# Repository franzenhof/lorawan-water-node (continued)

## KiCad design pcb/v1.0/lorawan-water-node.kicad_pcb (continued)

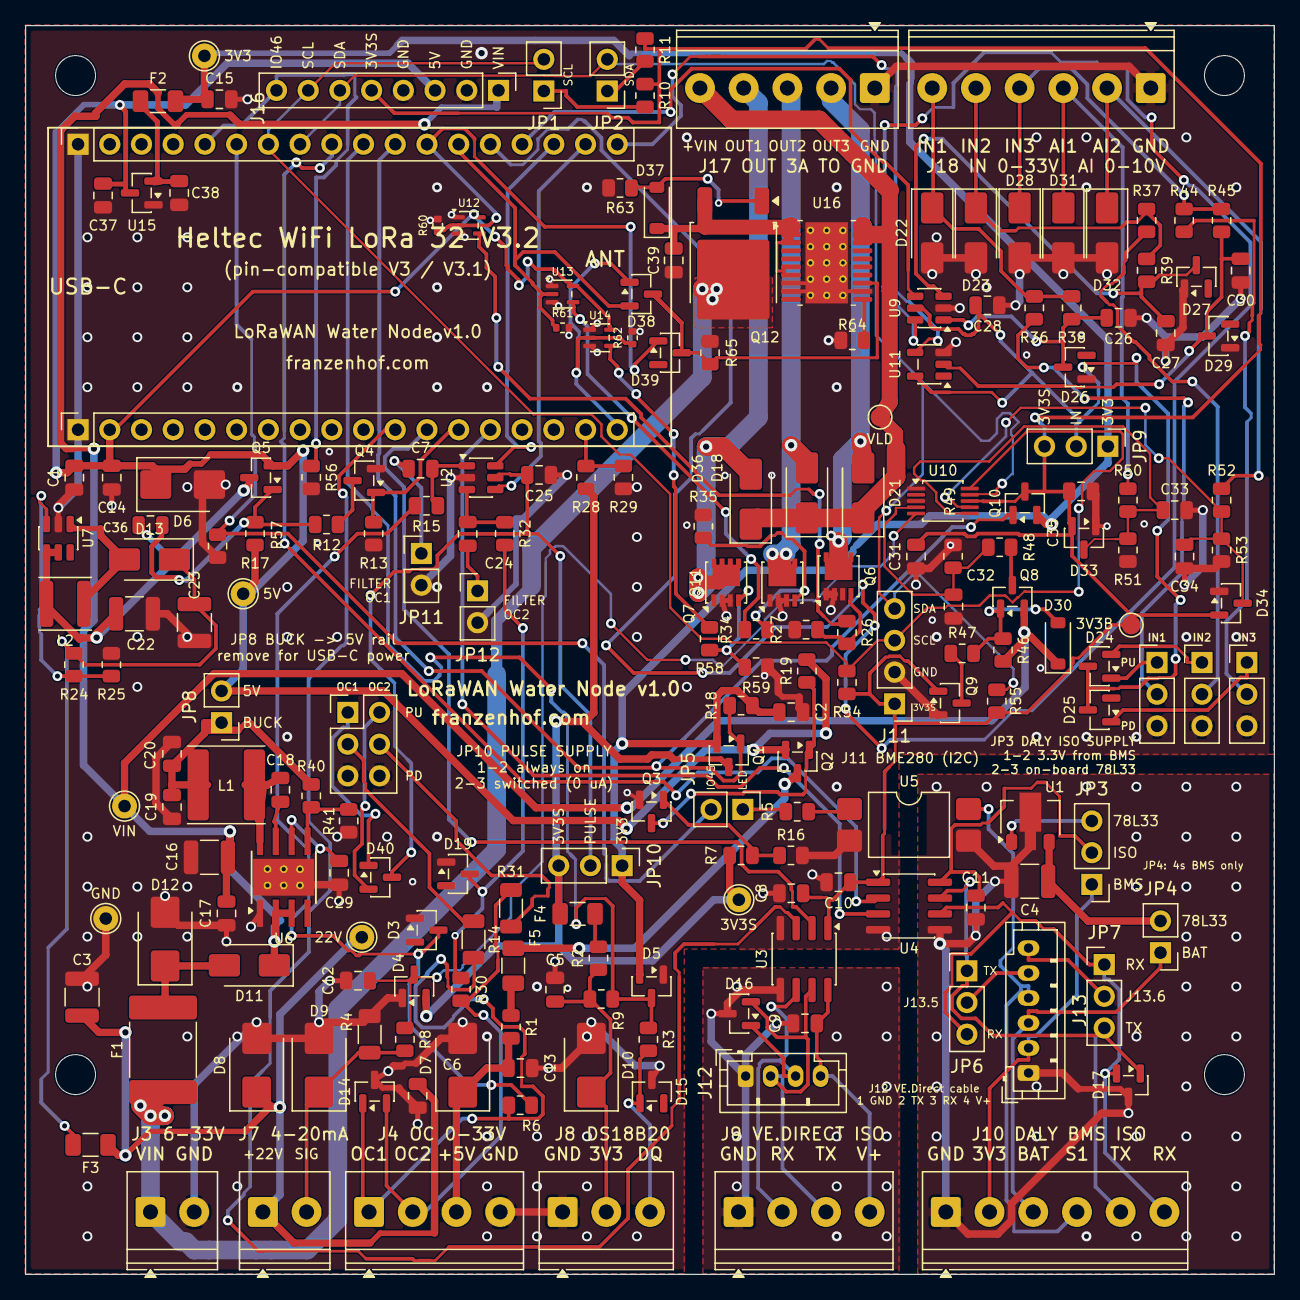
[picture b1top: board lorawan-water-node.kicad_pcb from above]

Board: 2 copper layers, 100.0 x 100.0 mm, 208 parts (0 on the bottom side), 118 nets.

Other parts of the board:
H1, H2, H3, H4: M3; MountingHole_3.2mm_M3

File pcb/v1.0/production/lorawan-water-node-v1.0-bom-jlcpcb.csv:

"Comment","Designator","Footprint","LCSC Part #","MPN"
"22uF 25V","C1,C2,C19,C20","Capacitor_SMD:C_0805_2012Metric","C45783","Samsung CL21A226MAQNNNE (25V X5R)"
"10uF 50V","C3,C4,C22,C23","Capacitor_SMD:C_1210_3225Metric","C596319","Yageo CC1210KKX7R9BB106"
"100nF","C5,C6,C8,C9,C10,C11,C12,C13,C14,C15,C18,C25,C26,C27,C28,C30,C31,C32,C33,C34,C35","Capacitor_SMD:C_0805_2012Metric","C49678","Yageo CC0805KRX7R9BB104"
"47nF","C7,C24","Capacitor_SMD:C_0805_2012Metric","C53134","Samsung CL21B473KBCNNNC (50V X7R, basic)"
"10uF 100V","C16","Capacitor_SMD:C_1210_3225Metric","C5156756","FS32X106K101EGG (100V X7R 1210)"
"220nF 100V","C17","Capacitor_SMD:C_0805_2012Metric","C513710","Yageo CC0805KKX7R0BB224 (100V X7R)"
"1uF","C29,C36,C37,C38","Capacitor_SMD:C_0805_2012Metric","C28323","Samsung CL21B105KBFNNNE (50V X7R)"
"100nF 100V","C39","Capacitor_SMD:C_0805_2012Metric","C28233","Samsung CL21B104KCFNNNE (100V X7R)"
"BZX84C5V6","D3,D19,D26,D27,D29","Package_TO_SOT_SMD:SOT-23","C82471","onsemi BZX84C5V6LT1G"
"BAT54S","D4,D5,D33,D34","Package_TO_SOT_SMD:SOT-23","C7420333","R+O BAT54S (preferred)"
"SMBJ6.0A","D6,D7","Diode_SMD:D_SMB","C113976","SMBJ6.0A"
"SMBJ24A","D8","Diode_SMD:D_SMB","C123819","SMBJ24A"
"SMBJ5.0A","D9","Diode_SMD:D_SMB","C78423","SMBJ5.0A"
"SMLVT3V3","D10","Diode_SMD:D_SMB","C283619","SMLVT3V3"
"SS210","D11,D13,D18,D21,D36","Diode_SMD:D_SMA","C14996","SS210 (100 V 2 A Schottky, basic)"
"SMBJ33CA","D12","Diode_SMD:D_SMB","C78420","SMBJ33CA (bidirectional)"
"PESD36VS2UT","D14","Package_TO_SOT_SMD:SOT-23","C85381","Nexperia PESD36VS2UT,215 (36 V, 2 lines)"
"PESD5V0S2BT","D15,D16,D17","Package_TO_SOT_SMD:SOT-23","C49338","Nexperia PESD5V0S2BT,215"
"SMAJ33CA","D22,D23,D28,D31,D32","Diode_SMD:D_SMA","C115251","SMAJ33CA (400 W, bidirectional)"
"BAS70-06","D24,D25,D40","Package_TO_SOT_SMD:SOT-23","C8651","Nexperia BAS70-06,215 (70 V Schottky, common anode)"
"BZT52C12","D30,D37","Diode_SMD:D_SOD-123","C19077410","BZT52C12 (preferred)"
"BAV70","D38,D39","Package_TO_SOT_SMD:SOT-23","C68978","BAV70 (common cathode, basic)"
"PTC 1.1A 60V","F1","Fuse:Fuse_2920_7451Metric","C3020148","BHFUSE BSMD2920-100-60V"
"PTC 0.25A","F2","Fuse:Fuse_1206_3216Metric","C70068","nSMD025 (16V)"
"PTC 0.05A","F3,F4","Fuse:Fuse_1206_3216Metric","C7542924","Littelfuse 1206L005/60NR (60V)"
"PTC 0.1A","F5","Fuse:Fuse_1206_3216Metric","C70065","nSMD010 (60V)"
"22uH","L1","Inductor_SMD:L_Sunlord_SWPA6045S","C83454","Sunlord SWPA6045S220MT"
"22uH","L2","Inductor_SMD:L_Sunlord_SWPA4030S","C83472","Sunlord SWPA4030S220MT"
"AO3401A","Q1,Q2,Q5,Q10","Package_TO_SOT_SMD:SOT-23","C15127","AO3401A"
"AO3400A","Q3,Q4","Package_TO_SOT_SMD:SOT-23","C20917","AOS AO3400A"
"AON7264E","Q6,Q7,Q11","Package_SO:Vishay_PowerPAK_1212-8_Single","C431191","AOS AON7264E (60 V N-MOSFET, DFN 3.3x3.3)"
"SI2309CDS","Q8","Package_TO_SOT_SMD:SOT-23","C10493","Vishay SI2309CDS-T1-GE3"
"2N7002","Q9","Package_TO_SOT_SMD:SOT-23","C8545","2N7002 (60 V)"
"NCE60P50K","Q12","Package_TO_SOT_SMD:TO-252-2","C130104","NCE60P50K (60 V P-MOSFET, TO-252)"
"10","R1,R2","Resistor_SMD:R_0805_2012Metric","C17415","UniOhm 0805W8F100JT5E"
"33","R3","Resistor_SMD:R_0805_2012Metric","C17634","UniOhm 0805W8F330JT5E"
"120 0.1%","R4","Resistor_SMD:R_1206_3216Metric","C870389","Yageo RT1206BRD07120RL"
"220","R5,R26,R34,R58","Resistor_SMD:R_0805_2012Metric","C17557","UniOhm 0805W8F2200T5E"
"10k","R6,R13,R16,R17,R25,R30,R49,R54,R55","Resistor_SMD:R_0805_2012Metric","C17414","UniOhm 0805W8F1002T5E"
"1k","R7,R8","Resistor_SMD:R_0805_2012Metric","C17513","UniOhm 0805W8F1001T5E"
"2.2k","R9","Resistor_SMD:R_0805_2012Metric","C17520","UniOhm 0805W8F2201T5E"
"4.7k","R10,R11,R12,R15,R32","Resistor_SMD:R_0805_2012Metric","C17673","UniOhm 0805W8F4701T5E"
"10k","R14,R31","Resistor_SMD:R_1206_3216Metric","C17902","UniOhm 1206W4F1002T5E (250 mW)"
"100k","R18,R19,R27,R28,R29,R35,R36,R37,R40,R44,R46,R48,R50,R52,R56,R57,R59","Resistor_SMD:R_0805_2012Metric","C149504","UniOhm 0805W8F1003T5E"
"360k","R24","Resistor_SMD:R_0805_2012Metric","C17645","UniOhm 0805W8F3603T5E"
"47k","R38,R39,R45,R47,R51,R53,R65","Resistor_SMD:R_0805_2012Metric","C17713","UniOhm 0805W8F4702T5E"
"24.9k","R41","Resistor_SMD:R_0805_2012Metric","C17571","UniOhm 0805W8F2492T5E"
"100k","R60,R61,R62","Resistor_SMD:R_0402_1005Metric","C25741","UniOhm 0402WGF1003TCE"
"1M","R63","Resistor_SMD:R_0805_2012Metric","C17514","UniOhm 0805W8F1004T5E"
"3.3k","R64","Resistor_SMD:R_0805_2012Metric","C26010","UniOhm 0805W8F3301T5E"
"78L33","U1","Package_TO_SOT_SMD:SOT-89-3","C14170","ST L78L33ACUTR (SOT-89)"
"SN74LVC2G14DBVR","U2,U9","Package_TO_SOT_SMD:SOT-23-6","C12401","TI SN74LVC2G14DBVR"
"ADuM121N1BRZ","U3,U4","Package_SO:SOIC-8_3.9x4.9mm_P1.27mm","C190783","ADUM121N1BRZ-RL7 (alt. ISO7721DR C366164)"
"PC817 SMD","U5","Package_DIP:SMDIP-4_W9.53mm","C3025164","Goodwork PC817C (SMD-4)"
"LMR36510ADDAR","U6","Package_SO:Texas_HTSOP-8-1EP_3.9x4.9mm_P1.27mm_EP2.95x4.9mm_Mask2.4x3.1mm_ThermalVias","C1858393","TI LMR36510ADDAR (4.2-65 V, 1 A buck)"
"MT3608","U7","Package_TO_SOT_SMD:SOT-23-6","C84817","Aerosemi MT3608"
"ADS1115IDGSR","U10","Package_SO:TSSOP-10_3x3mm_P0.5mm","C37593","TI ADS1115IDGSR"
"SN74LVC1G14DBVR","U11","Package_TO_SOT_SMD:SOT-23-5","C7835","TI SN74LVC1G14DBVR"
"SN74AHCT1G125DCKR","U12,U13,U14","Package_TO_SOT_SMD:SOT-353_SC-70-5","C350557","TI SN74AHCT1G125DCKR (SC-70-5)"
"XC6206P332MR","U15","Package_TO_SOT_SMD:SOT-23","C5446","Torex XC6206P332MR-G (basic)"
"TPS16630PWPR","U16","Package_SO:HTSSOP-20-1EP_4.4x6.5mm_P0.65mm_EP3.4x6.5mm_Mask2.96x2.96mm_ThermalVias","C1849461","TI TPS16630PWPR (60 V 6 A eFuse, HTSSOP-20)"

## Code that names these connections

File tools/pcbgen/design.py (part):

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
# ---------------- Heltec WiFi LoRa 32 V3 -----------------------------------
j1 = {str(i): None for i in range(1, 19)}
j1.update({"1": "GND", "2": "+5V", "11": "VE_ESP_TX", "12": "VE_ESP_RX", "13": "GPIO47", "14": "DALY_ESP_TX", "17": "HW_ID", "18": "OUT1_G"})
P("J1", conn(18), "Heltec V3 header (5V side)", SOCK18, j1, "HELTEC_L", "MCU",
  "Heltec pins: 1 GND, 2 5V, 11 GPIO34, 12 GPIO33, 13 GPIO47, 14 GPIO48, 17 GPIO20, 18 GPIO19", lcsc_key="SOCK18")
j2 = {str(i): None for i in range(1, 19)}
j2.update({"1": "GND", "2": "3V3_HELTEC", "5": "GPIO46", "6": "GPIO45", "7": "SCL", "8": "SDA", "9": "DALY_ESP_RX",
           "10": "ONEWIRE_IO", "11": "GPIO38", "12": "OUT3_G", "13": "OUT2_G", "14": "DIN1_OUT", "15": "DIN2_OUT",
           "16": "FLOW_OUT", "17": "FLOW2_OUT", "18": "DIN3_OUT"})
P("J2", conn(18), "Heltec V3 header (3V3 side)", SOCK18, j2, "HELTEC_R", "MCU",
  "Heltec pins: 1 GND, 2 3V3, 5 GPIO46, 6 GPIO45, 7 GPIO42, 8 GPIO41, 9 GPIO40, 10 GPIO39, 11 GPIO38, 12-18 GPIO1-7",
  lcsc_key="SOCK18")

# ---------------- Power input VIN 6-33 V (4s/8s LiFePO4, 12/24 V lead, 24 V PLC supply) -> 5 V / 3.3 V
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P("C16", ("Device", "C"), "10uF 100V", C1210, {"1": "+VIN", "2": "GND"}, None, "Power")
P("C17", ("Device", "C"), "220nF 100V", C0805, {"1": "+VIN", "2": "GND"}, None, "Power", "HF input capacitor at the VIN pin (220 nF per TI datasheet 8.2.1.2.5)")
P("C18", ("Device", "C"), "100nF", C0805, {"1": "BUCK_BST", "2": "BUCK_SW"}, None, "Power", "bootstrap")
P("C29", ("Device", "C"), "1uF", C0805, {"1": "BUCK_VCC", "2": "GND"}, None, "Power", "internal LDO (VCC pin)")
# Isat must exceed the LMR36510 low-side current limit (up to 1.6 A): SWPA4030 (1.3 A) is too small
P("L1", ("Device", "L"), "22uH", "Inductor_SMD:L_Sunlord_SWPA6045S", {"1": "BUCK_SW", "2": "+5V_BUCK"}, None, "Power", "Sunlord SWPA6045S220MT (Isat 2.05 A)", lcsc_key="L22u6045")
P("R40", ("Device", "R"), "100k", R0805, {"1": "+5V_BUCK", "2": "BUCK_FB"}, None, "Power", "feedback divider top")
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P("D38", ("Diode", "BAV70"), "BAV70", SOT23, {"1": "OUT1_G", "2": "OUT2_G", "3": "EF_SHDN"}, None, "Load eFuse", "OUT1 / OUT2 -> U16 SHDN")
P("D39", ("Diode", "BAV70"), "BAV70", SOT23, {"1": "OUT3_G", "2": None, "3": "EF_SHDN"}, None, "Load eFuse", "OUT3 -> U16 SHDN")
P("R65", ("Device", "R"), "47k", R0805, {"1": "EF_SHDN", "2": "GND"}, None, "Load eFuse", "U16 SHDN pull-down (off while all outputs are off)")
# channel order follows the board from left to right (J17 OUT1 | OUT2 | OUT3 above Q11 | Q7 | Q6): OUT1 = GPIO19, OUT3 = GPIO1
for n, (q, rs, rp, d, gpio, u, rd) in enumerate((("Q11", "R58", "R59", "D36", "GPIO19", "U14", "R62"),
                                                 ("Q7", "R34", "R35", "D18", "GPIO2", "U13", "R61"),
                                                 ("Q6", "R26", "R27", "D21", "GPIO1", "U12", "R60")), 1):
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P("R28", ("Device", "R"), "100k", R0805, {"1": "+3V3_SW", "2": "HW_ID"}, None, "MCU", "HW revision ID (top), v1.0: 100k")
P("R29", ("Device", "R"), "100k", R0805, {"1": "HW_ID", "2": "GND"}, None, "MCU", "HW revision ID (bottom), v1.0: 100k -> 0.50 * 3V3")
# strapping pins used as I/O: must stay LOW at boot
P("R56", ("Device", "R"), "100k", R0805, {"1": "GPIO46", "2": "GND"}, None, "MCU", "GPIO46 (strapping pin, J16) LOW at boot")
P("R57", ("Device", "R"), "100k", R0805, {"1": "GPIO45", "2": "GND"}, None, "MCU", "GPIO45 (strapping pin, DALY S1) LOW at boot")

# ---------------- test points and expansion header
# test points: single solder pads (1.0 mm hole, takes a header pin or a probe) next to each rail
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# VIN at the end with GND as its only neighbour (a slipped probe / jumper cannot put VIN onto I2C or 5V);
# 5V between two GND pins; pins 4-7 = GND | 3V3S | SDA | SCL fit common 4-pin I2C modules
P("J16", conn(8), "Expansion", HDR.format(n=8),
  {"1": "+VIN", "2": "GND", "3": "+5V", "4": "GND", "5": "+3V3_SWB", "6": "SDA", "7": "SCL", "8": "GPIO46"},
  None, "MCU", "I2C (switched 3.3 V domain) + GPIO46, 3.3 V logic, unprotected", lcsc_key="HDR8")

# ---------------- Switched 3.3 V rail (GPIO38, LOW = on) ---------------------
# two parallel switches, both on GPIO38: +3V3_SW (1-Wire, pulse inputs, HW-ID, 5 V sensor rail) and
# +3V3_SWB (I2C domain, ADS1115, digital inputs, isolators) - keeps both nets short on the board
P("Q1", ("Transistor_FET", "AO3401A"), "AO3401A", SOT23, {"1": "GPIO38", "2": "+3V3", "3": "+3V3_SW"}, "LP0701N3-G", "Switched rails")
P("Q10", ("Transistor_FET", "AO3401A"), "AO3401A", SOT23, {"1": "GPIO38", "2": "+3V3", "3": "+3V3_SWB"}, None, "Switched rails", "2nd switched 3.3 V rail (I2C / analog / inputs)")
P("C35", ("Device", "C"), "100nF", C0805, {"1": "+3V3_SWB", "2": "GND"}, None, "Switched rails")
P("R18", ("Device", "R"), "100k", R0805, {"1": "+3V3", "2": "GPIO38"}, "R18", "Switched rails")
P("C8", ("Device", "C"), "100nF", C0805, {"1": "+3V3_SWB", "2": "GND"}, "C8", "Switched rails")
P("C10", ("Device", "C"), "100nF", C0805, {"1": "+3V3_SWB", "2": "GND"}, "C10", "Switched rails")

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P("JP10", conn(3), "PULSE supply: 1-2 3V3, 2-3 3V3 switched", HDR.format(n=3), {"1": "+3V3", "2": "PULSE_VCC", "3": "+3V3_SW"}, None, "Flow",
  "1-2 = pulse stage powered in deep sleep (no deep-sleep counter in the firmware yet), 2-3 = off in deep sleep (0 uA)", lcsc_key="HDR3")

# ---------------- 24 V boost supply switch: +5V -> MT3608 (GPIO47, HIGH = on) -------
# fed from the 5 V rail, so the 4-20 mA loop works with any VIN (6-33 V) and on USB power
P("Q5", ("Transistor_FET", "AO3401A"), "AO3401A", SOT23,
  {"1": "HS_GATE", "2": "+5V", "3": "BOOST_IN"}, None, "High-side", "P-MOSFET: switches the 24 V boost input")
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# ~13 mA charging current for the 25 uF behind Q5 instead of an amp-level dump from the 5 V rail
P("C36", ("Device", "C"), "1uF", C0805, {"1": "BOOST_IN", "2": "HS_GATE"}, None, "High-side", "Q5 soft start (gate-drain)")
P("R12", ("Device", "R"), "4.7k", R0805, {"1": "HS_GATE", "2": "HS_DRV"}, "R12", "High-side")
P("Q4", ("Transistor_FET", "AO3400A"), "AO3400A", SOT23, {"1": "GPIO47", "2": "GND", "3": "HS_DRV"}, "TN2106N3-G@606", "High-side")
P("R13", ("Device", "R"), "10k", R0805, {"1": "GPIO47", "2": "GND"}, "R13", "High-side")

# 5 V -> 24 V boost for the 4-20 mA loop (only powered while Q5 is on)
P("U7", ("Regulator_Switching", "MT3608"), "MT3608", "Package_TO_SOT_SMD:SOT-23-6",
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  {"1": "REG_OUT", "2": "GND_DALY", "3": "REG_IN"}, "78Lxx", "DALY",
  "ST L78L33ACUTR, SOT-89 (1 OUT, 2 GND, 3 IN): 3.3 V like the DALY UART; input max 30 V -> JP4 only with a 4s BMS")
P("C4", ("Device", "C"), "10uF 50V", C1210, {"1": "REG_IN", "2": "GND_DALY"}, "C4", "DALY")
P("JP5", conn(2), "DALY wakeup enable", HDR.format(n=2), {"1": "PC817_LED", "2": "GPIO45"}, "GPIO45", "DALY", lcsc_key="HDR2")
P("R5", ("Device", "R"), "220", R0805, {"1": "PC817_LED", "2": "PC817_A"}, "R5", "DALY")
P("U5", ("Isolator", "EL817"), "PC817 SMD", "Package_DIP:SMDIP-4_W9.53mm",
  {"1": "PC817_A", "2": "GND", "3": "GND_DALY", "4": "DALY_S1"}, "PC817", "DALY", lcsc_key="PC817")

MOUNTING_HOLES_IN = [(0.1623, 0.1335), (3.5623, 0.7335), (3.8623, 1.9335)]  # from rev10 drill file, inch, y up
BOARD_MIL = (3937.0, 2362.2)  # prototype board, 100 x 60 mm (v1.0: 100 x 100 mm, see layout_v6.py)
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
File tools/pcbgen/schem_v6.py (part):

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FLAG_AT = (70, 52)
LABEL_PARTS = ["J1", "J2", "J3", "J4", "J7", "J8", "J9", "J10", "J11", "J12", "J13", "J16", "J17", "J18",
               "JP3", "JP4", "JP5", "JP6", "JP7", "JP9", "JP10", "JP13", "JP14", "JP15", "JP16", "U10"]
LABEL_ONLY_NETS = ["BOOST_FB", "DIN_VCC", "PULSE_VCC", "BUCK_VCC"]
LABEL_AT = {("F1", "1"): True, ("R4", "1"): True, ("C13", "1"): True, ("C5", "1"): True, ("D18", "2"): True,
            ("D21", "2"): True, ("D36", "2"): True, ("D22", "1"): True, ("D23", "1"): True, ("R18", "2"): True}

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        ("TP6", 59, 47, VF), ("TP7", 47, 53, VF), ("TP8", 53, 53, VF)],
        notes=[(3, 7, "J1 = header on the 5 V side, J2 = header on the 3V3 side (pin 1 = GND, USB-C end)\n"
                      "V3 / V3.1 / V3.2 are pin-compatible"),
               (3, 42, "HW revision ID (GPIO20): v1.0 = 100k / 100k -> 0.5 x 3V3\nR56 / R57: strapping pins GPIO46 / GPIO45 LOW at boot"),
               (22, 60, "J16 expansion header (I2C on 3V3S, GPIO46), TP1-TP8 test pads (not populated)")]),
    dict(title="Power supply: VIN 6-33 V -> 5 V buck, 3.3 V", x=68, y=0, w=96, h=46, parts=[
        ("J3", 5, 10, M),
        ("F1", 12, 9, H), ("D12", 16, 10.5, DK), ("D11", 21, 9, DH), ("C16", 25, 12, V), ("C17", 28, 12, V),
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        notes=[(70, 8, "LMR36510: 4.2-65 V in, 5 V / 1 A out, Iq 26 uA\nVout = 1.0 V x (1 + 100k / 24.9k) = 5.02 V\nVIN: PTC 1.1 A 60 V, TVS SMBJ33A, reverse diode SS34"),
               (50, 20, "JP8 on = buck supplies 5 V (normal)\nJP8 off = Heltec USB-C only (bench test)"),
               (33, 32, "3.3 V sensor rail: own LDO XC6206 (Iq 1 uA) from 5 V, PTC 250 mA\nHeltec 3V3 supplies only the module")]),
    dict(title="4-20 mA level sensor: 5 V -> 24 V boost switched by GPIO47", x=166, y=0, w=76, h=52, parts=[
        ("Q5", 6, 10, PF), ("R17", 11, 8.5, V), ("R12", 18, 10, H), ("Q4", 22, 12), ("R13", 18, 13.5, V), ("C36", 14, 15.5, V),
        ("C22", 12, 21.5, V), ("L2", 24, 17, H), ("U7", 24, 21), ("D13", 31, 20, DH), ("C23", 35, 21.5, V),
        ("R24", 39, 21.5, V), ("R25", 43, 27.5, V), ("F3", 48, 20, H),
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        ("Q10", 30, 26, PF), ("C35", 36, 28, V),
        ("R7", 10, 24.5, V), ("Q3", 14, 26), ("R16", 10, 29.5, V),
        ("Q2", 20, 22, PFL), ("R19", 16, 20.5, V)],
        notes=[(3, 34, "GPIO38 LOW = +3V3_SW and +3V3_SWB on\n+5V_FLOW follows +3V3_SW")]),
    dict(title="Pulse inputs (flow sensor + 2nd input)", x=0, y=64, w=66, h=48, parts=[
        ("J4", 4, 30, M), ("D14", 12, 15, {"a": 90}),
        ("R30", 17, 9, H), ("R31", 9, 8, V), ("D19", 24, 11, DK), ("R32", 30, 9, H), ("C24", 34, 10.5, V), ("JP12", 36, 15),
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        ("D18", 35, 31.5, DK), ("Q7", 26, 36), ("R34", 19, 36, H), ("U13", 11, 36), ("R61", 5, 37.5, V), ("R35", 22, 37.5, V),
        ("D21", 35, 45.5, DK), ("Q6", 26, 50), ("R26", 19, 50, H), ("U12", 11, 50), ("R60", 5, 51.5, V), ("R27", 22, 51.5, V)],
        notes=[(2, 4, "Q12: reverse-\npolarity P-FET\nD37: gate clamp\n-> eFuse U16"),
               (3, 56, "J17: +VIN | OUT1 | OUT2 | OUT3 | GND, max 3 A each, 3 A total (eFuse U16: 5.4 A limit for start currents)\nGPIO19 = OUT1, GPIO2 = OUT2, GPIO1 = OUT3 (HIGH = on)\nU12-U14 74AHCT1G125: 5 V gate drive, R60-R62 off at reset")]),
    dict(title="Load supply eFuse (+VIN_LOAD)", x=258, y=64, w=46, h=50, parts=[
        ("U16", 22, 20), ("C39", 6, 13, V), ("R64", 34, 27, V),
        ("D38", 14, 38), ("D39", 14, 44), ("R65", 30, 42, V)],
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        ("U1", 16, 36), ("C4", 10, 37.5, V),
        ("R5", 26, 35, H), ("U5", 34, 36), ("J10", 70, 14), ("J13", 70, 25),
        ("JP4", 4, 36, M), ("JP3", 26, 42, M), ("JP5", 18, 30, M), ("JP6", 54, 42), ("JP7", 62, 42)],
        notes=[(44, 30, "J10 / J13: GND | 3V3 | 12V | S1 | TX | RX\nJP3 DALY VDD: 1-2 BMS 3.3 V, 2-3 78L33 (4s BMS only)\nJP4: 78L33 on, JP5: wake-up via GPIO45\n"
                        "JP6 / JP7: J13 pin 5/6\n  1-2 = 1:1 cable, 2-3 = crossed cable")]),
]

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
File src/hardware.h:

// Shared by every module. Pins and fixed hardware constants of the
// lorawan-water-node PCB v1.0 (Heltec WiFi LoRa 32 V3).
#pragma once
#include <Arduino.h>

// ============================================================================
// PIN ASSIGNMENT
// ============================================================================
// Every input, pulse input and output sits on an RTC GPIO (0-21): inputs can
// wake the chip from deep sleep, outputs are held per pin through deep sleep.
// UARTs, 1-Wire and I2C use the remaining (non-RTC) pins.
constexpr int PIN_USER_BUTTON      =  0;  // After boot: hold 3 s → config portal; during sleep: EXT0 wakeup
constexpr int PIN_OUT3             =  1;  // J17 OUT3 low-side switch (3 A), HIGH = on (driver input pull-down)
                                          //   GPIO1 also carries the Heltec VBAT divider -> output only
constexpr int PIN_OUT2             =  2;  // J17 OUT2, same as OUT3
constexpr int PIN_DIN1             =  3;  // J18 IN1 via Schmitt trigger, inverted: terminal high = GPIO LOW
constexpr int PIN_DIN2             =  4;  // J18 IN2, same as IN1
constexpr int PIN_FLOW_SENSOR      =  5;  // J4 OC1 flow sensor pulses via Schmitt trigger (pulse = HIGH)
constexpr int PIN_PULSE2           =  6;  // J4 OC2, 2nd pulse input, same as OC1
constexpr int PIN_DIN3             =  7;  // J18 IN3, same as IN1
constexpr int PIN_OUT1             = 19;  // J17 OUT1, same as OUT3 (board order: OUT1 | OUT2 | OUT3 = GPIO19 | 2 | 1)
constexpr int PIN_HW_ID            = 20;  // revision ID divider from VCC3.3 switched (ADC2), v1.0: 0.5 x 3V3
constexpr int PIN_VICTRON_RX       = 33;  // VE.Direct UART RX (from Victron TX)
constexpr int PIN_VICTRON_TX       = 34;  // VE.Direct UART TX
constexpr int PIN_OPTO_SWITCH      = 38;  // VCC3.3 switched + 5V flow sensor rail, LOW = on:
                                          //   GPIO38 → AO3401A gate (direct)
                                          //   VCC3.3_SW → AO3400A → AO3401A → flow sensor 5V rail
                                          //   (the N-MOSFET re-inverts so the 5V rail also turns on when GPIO38 LOW)
                                          //   VCC3.3_SW also powers the I2C domain (BME280, ADS1115) and
                                          //   switches the VIN divider of the ADS1115
constexpr int PIN_ONE_WIRE         = 39;  // DS18B20 1-Wire bus
constexpr int PIN_DALY_RX          = 40;  // DALY BMS UART RX
constexpr int PIN_I2C_SDA          = 41;  // BME280, ADS1115
constexpr int PIN_I2C_SCL          = 42;  // BME280, ADS1115
constexpr int PIN_DALY_TRIGGER     = 45;  // DALY BMS S1 wakeup (via JP5 + PC817, inverted); strapping pin, pull-down
constexpr int PIN_HIGH_SIDE_SWITCH = 47;  // HIGH = on: 5 V -> MT3608 boost (22 V supply of the 4-20 mA loop)
constexpr int PIN_DALY_TX          = 48;  // DALY BMS UART TX

// PC817 inverted: GPIO HIGH -> LED conducts -> S1 pulled LOW -> BMS wakes up
constexpr int DALY_S1_ACTIVE   = HIGH;
constexpr int DALY_S1_INACTIVE = LOW;

// ============================================================================
// ADS1115 (I2C 0x48, on VCC3.3 switched)
// ============================================================================
constexpr uint8_t ADS_ADDR      = 0x48;
constexpr uint8_t ADS_CH_VIN    = 0;      // VIN via 100k / 10k (switched by Q8)
constexpr uint8_t ADS_CH_LEVEL  = 1;      // 4-20 mA shunt R4 via 1k
constexpr uint8_t ADS_CH_AI1    = 2;      // J18 AI1, 0-10 V via 100k / 47k
constexpr uint8_t ADS_CH_AI2    = 3;      // J18 AI2, same as AI1
constexpr float   VIN_DIVIDER   = 11.0f;              // (100k + 10k) / 10k
constexpr float   AI_DIVIDER    = 147.0f / 47.0f;     // (100k + 47k) / 47k

// ============================================================================
// CONSTANTS
// ============================================================================
constexpr uint32_t WAKEUP_DELAY_MS      = 2000;
constexpr uint32_t DALY_WAKEUP_PULSE_MS =  200;
constexpr float    ADC_SHUNT_OHM        = 120.0f;  // R4 = 120 Ohm (max 20mA -> 2.4V)
constexpr float    LOOP_OVERCURRENT_MV  = 2760.0f; // 23 mA: shorted / faulty loop -> boost off (protects the 5 V rail)
// Hardware revision ID on GPIO20: divider from VCC3.3 switched (prototype: none, v1.0: 100k / 100k)
constexpr uint32_t HW_ID_V10_MIN_MV     = 1300;
constexpr uint32_t HW_ID_V10_MAX_MV     = 2000;
